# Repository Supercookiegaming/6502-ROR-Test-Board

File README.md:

# 6502-ROR-Test-Board

The 6502 ROR Test Board is a simple computer that tests if the ROR insruction is present on the 6502. I/O space is from 0x0000 to 0x7FFF. Rom space starts at 0x8000 and ends at 0xFFFF. The LED is tied to bit 7 and is set when the CPU R/W is low (writing). The data is then latched into the D-Latch and will be held until updated. The Yes ROR LED is turned on when the cpu writes to any memeory in the I/O space and bit 7 is high, all other bits do nothing. The No ROR LED is turned on whent he cpu writes to any memeory in the I/O space and bit 7 is low.
![ ][logo]

[logo]: https://github.com/Supercookiegaming/6502-ROR-Test-Board/blob/350ec1a620519f19180ad02e0bde4138ba3418b3/Renders/3D/KiCad%209%203D%206502%20ROR%20Test%20Board%20Render%20V2.0T.png
I used https://www.masswerk.at/6502/assembler.html to assemble the rom code and create a BIN file. When using https://www.masswerk.at/6502/# to emulate the board, use the code marked as "Emulator". When the ROR bug is enabled 0x0010 will be 00 and when it is disabled 0x0010 will be 80.

When Building your own board its best to use sockets.

V2.0S uses mostly SMD parts (mostly 0603). V2.0T only has through hole components. 

EasyEDA and KiCad 9 files are now available for both boards. 

The design is free for personally use only.

V2.0S and V2.0T both now support zif sockets for the 6502 and AT28C256, the imporved reset circuit design, ground M3 mounting points, and better silkscreen instructions and pinouts.

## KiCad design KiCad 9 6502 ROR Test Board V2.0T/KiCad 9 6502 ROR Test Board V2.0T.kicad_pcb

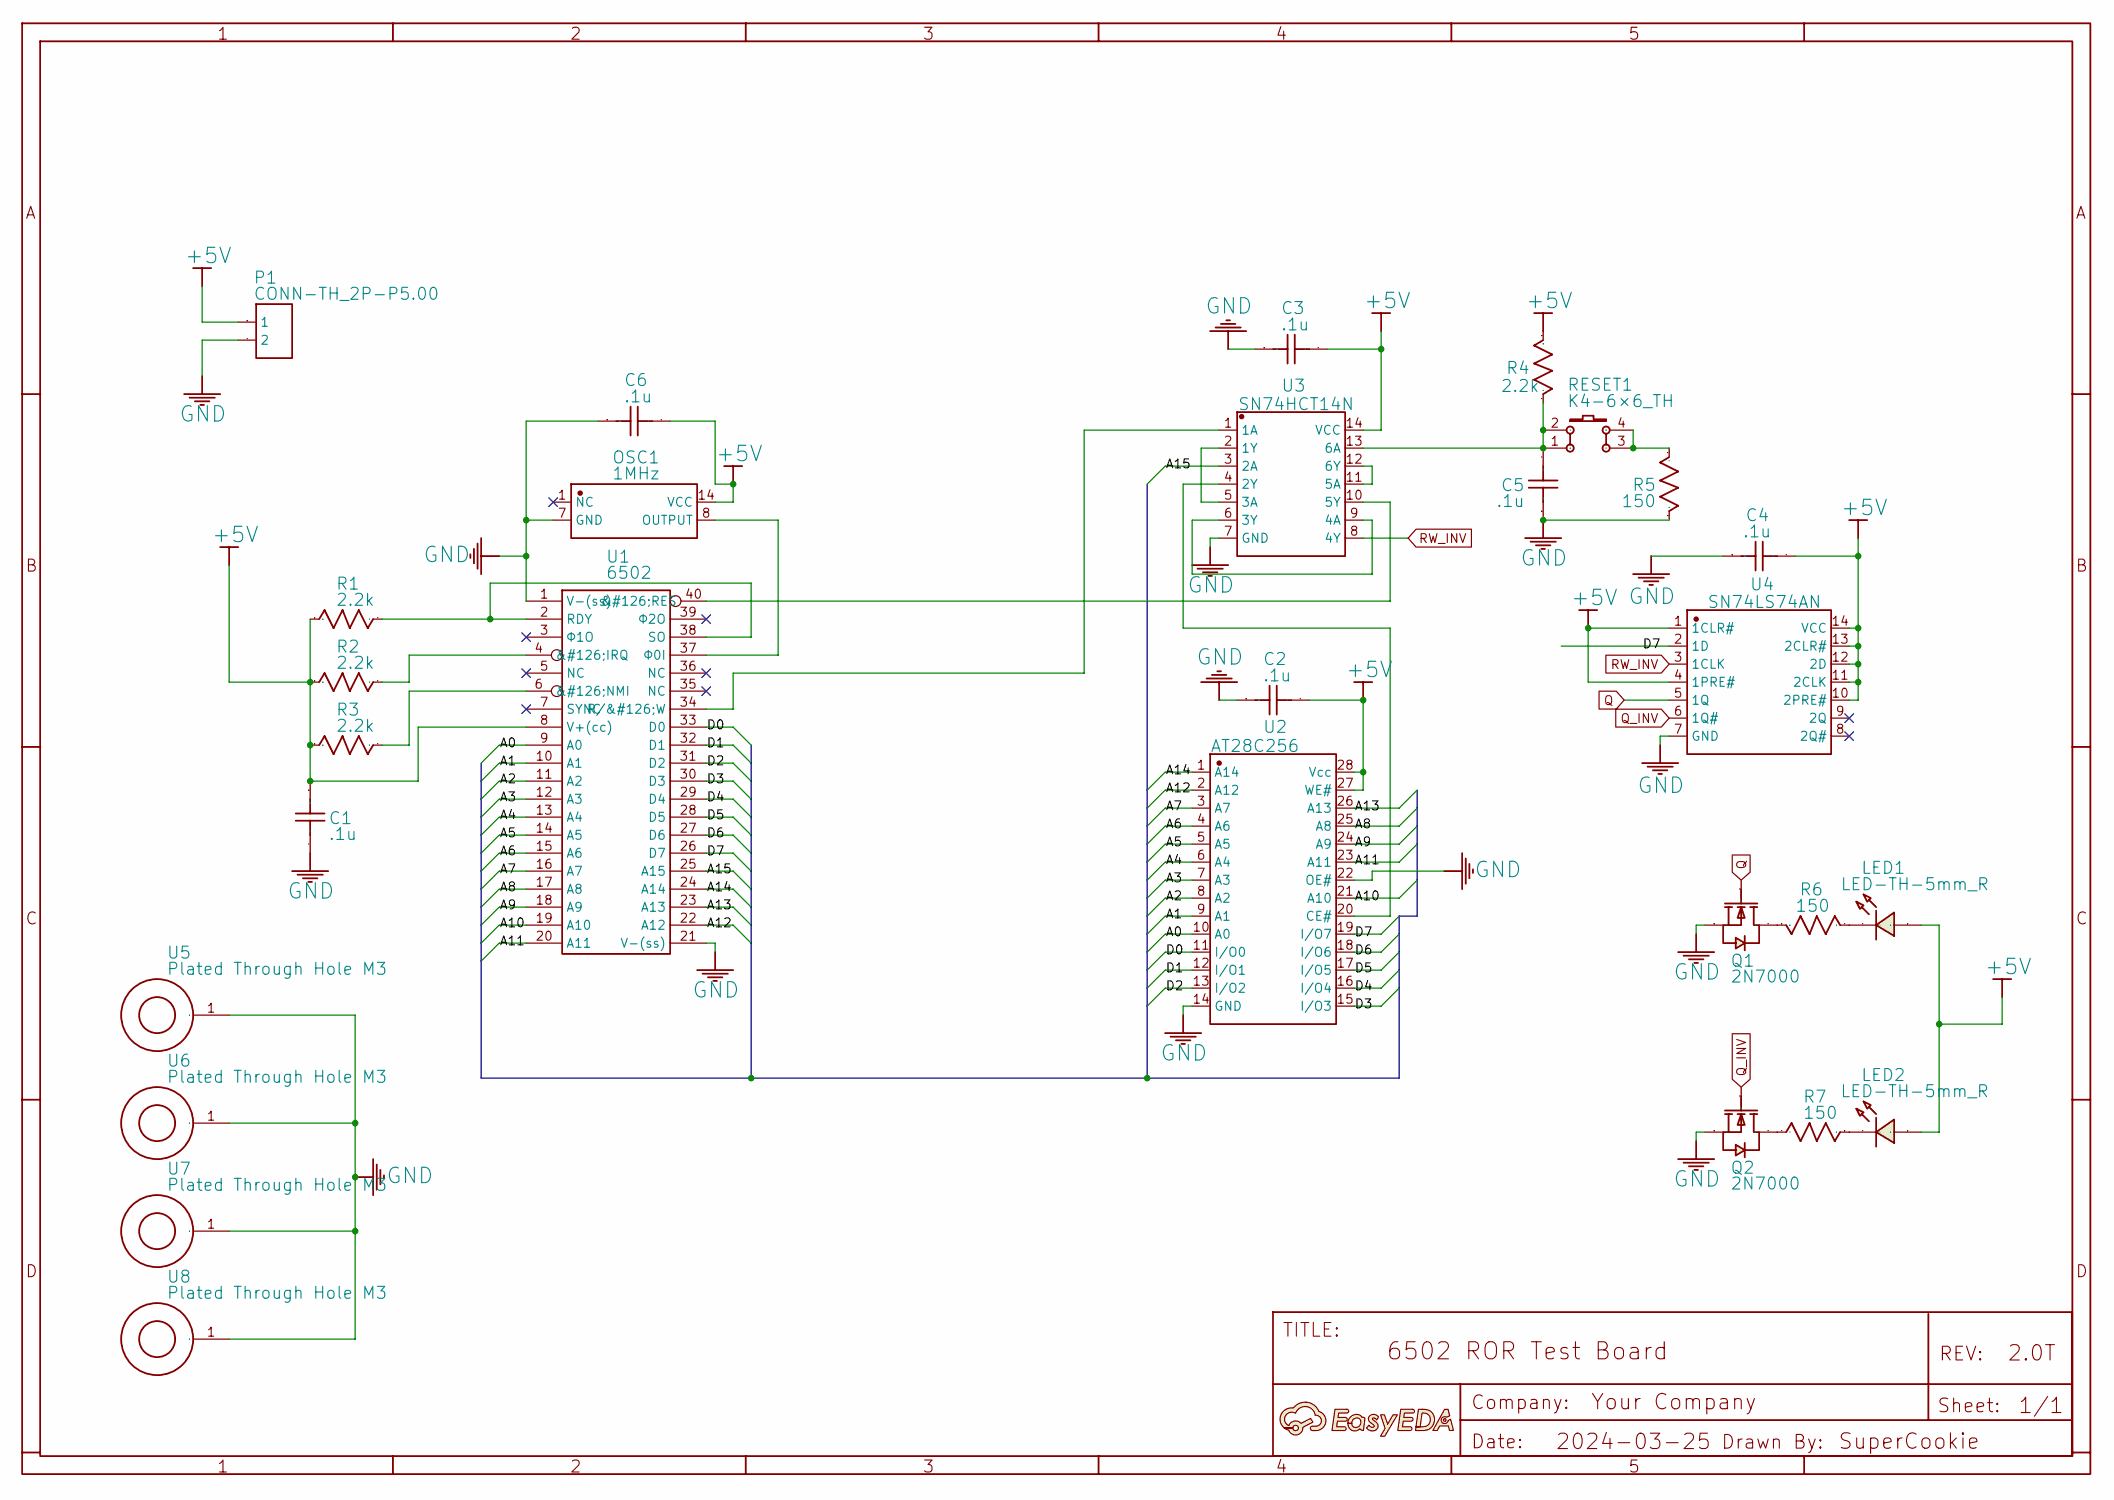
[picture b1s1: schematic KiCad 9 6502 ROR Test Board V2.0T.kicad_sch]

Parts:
A1: A; Manufacturer Part ?
C1, C2, C3, C4, C5, C6: .1u
LED1, LED2: LED-TH-5mm_R; Manufacturer Part 333-2SURD/S530-A3
OSC1: 1MHz; Manufacturer Part MXO45-3C-1M0000
P1: CONN-TH_2P-P5.00
Q1, Q2: 2N7000; Manufacturer Part 2N7002,215
R1, R2, R3, R4: 2.2k
R5, R6, R7: 150
RESET1: K4-6×6_TH; Manufacturer Part K2-1102DP-E4SW-04
U1: 6502
U2: AT28C256; Manufacturer Part AT28C256-15PU
U3: SN74HCT14N; Manufacturer Part SN74HCT14N
U4: SN74LS74AN; Manufacturer Part SN74LS74AN
U5, U6, U7, U8: Plated Through Hole M3

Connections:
+5V: C1.1, C2.2, C3.2, C4.2, C6.2, LED1.1, LED2.1, OSC1.14 (VCC), P1.1, R1.1, R2.1, R3.1, R4.1, U1.8 (V+(cc)), U2.27 (WE#), U2.28 (Vcc), U3.14 (VCC), U4.1 (1CLR#), U4.4 (1PRE#), U4.10 (2PRE#), U4.11 (2CLK), U4.12 (2D), U4.13 (2CLR#), U4.14 (VCC)
/A0: U1.9 (A0), U2.10 (A0)
/A1: U1.10 (A1), U2.9 (A1)
/A2: U1.11 (A2), U2.8 (A2)
/A3: U1.12 (A3), U2.7 (A3)
/A4: U1.13 (A4), U2.6 (A4)
/A5: U1.14 (A5), U2.5 (A5)
/A6: U1.15 (A6), U2.4 (A6)
/A7: U1.16 (A7), U2.3 (A7)
/A8: U1.17 (A8), U2.25 (A8)
/A9: U1.18 (A9), U2.24 (A9)
/A10: U1.19 (A10), U2.21 (A10)
/A11: U1.20 (A11), U2.23 (A11)
/A12: U1.22 (A12), U2.2 (A12)
/A13: U1.23 (A13), U2.26 (A13)
/A14: U1.24 (A14), U2.1 (A14)
/A15: U1.25 (A15), U3.3 (2A)
/D0: U1.33 (D0), U2.11 (I/O0)
/D1: U1.32 (D1), U2.12 (I/O1)
/D2: U1.31 (D2), U2.13 (I/O2)
/D3: U1.30 (D3), U2.15 (I/O3)
/D4: U1.29 (D4), U2.16 (I/O4)
/D5: U1.28 (D5), U2.17 (I/O5)
/D6: U1.27 (D6), U2.18 (I/O6)
/D7: U1.26 (D7), U2.19 (I/O7), U4.2 (1D)
GND: C1.2, C2.1, C3.1, C4.1, C5.1, C6.1, OSC1.7 (GND), P1.2, Q1.1 (S), Q2.1 (S), R5.1, U1.1 (V-(ss)), U1.21 (V-(ss)), U2.14 (GND), U2.22 (OE#), U3.7 (GND), U4.7 (GND), U5.1, U6.1, U7.1, U8.1
unnamed: LED1.2, R6.2
unnamed: LED2.2, R7.1
unnamed: OSC1.8 (OUTPUT), U1.37 (Φ0I)
unnamed: Q1.3 (D), R6.1
unnamed: Q2.3 (D), R7.2
unnamed: R5.2, RESET1.3, RESET1.4
unnamed: R2.2, U1.4 (&#126;IRQ)
unnamed: R3.2, U1.6 (&#126;NMI)
unnamed: U1.40 (&#126;RES), U3.10 (5Y)
unnamed: R1.2, U1.2 (RDY), U1.38 (SO)
unnamed: U1.34 (R/&#126;W), U3.1 (1A)
unnamed: U2.20 (CE#), U3.4 (2Y)
unnamed: U3.2 (1Y), U3.5 (3A)
unnamed: U3.6 (3Y), U3.9 (4A)
unnamed: U3.11 (5A), U3.12 (6Y)
Q: Q1.2 (G), U4.5 (1Q)
Q_INV: Q2.2 (G), U4.6 (1Q#)
R4_2: C5.2, R4.2, RESET1.1, RESET1.2, U3.13 (6A); also elsewhere on the board
RW_INV: U3.8 (4Y), U4.3 (1CLK)

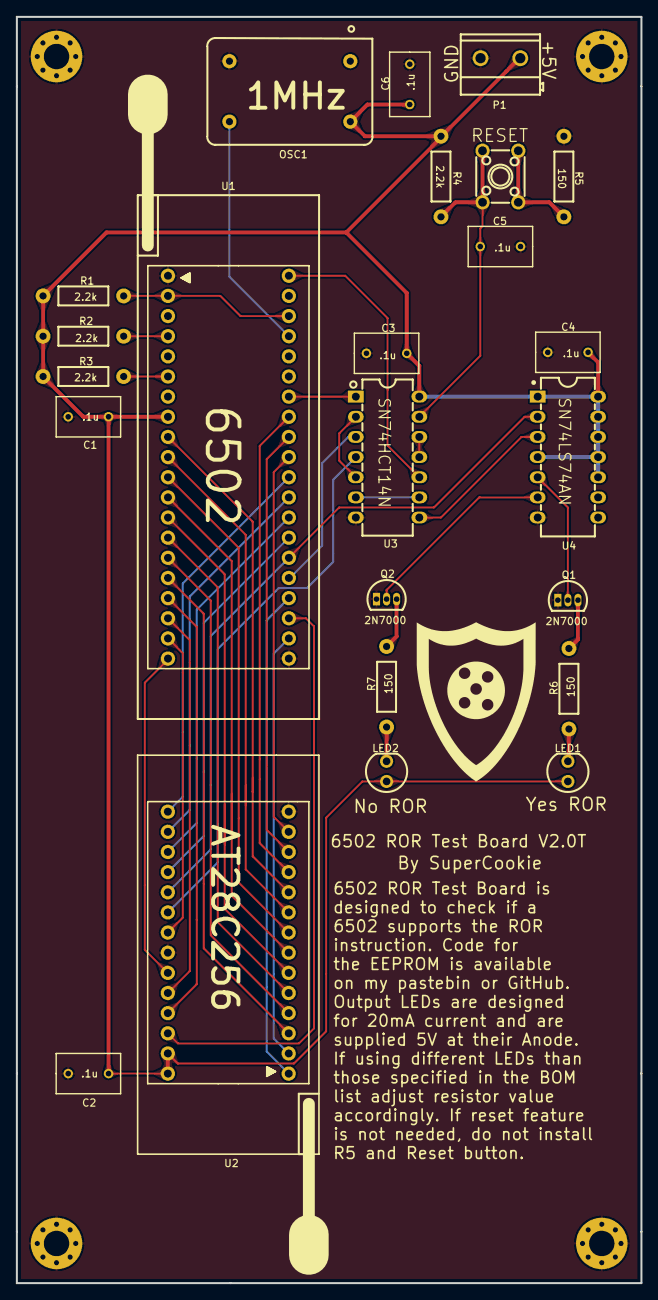
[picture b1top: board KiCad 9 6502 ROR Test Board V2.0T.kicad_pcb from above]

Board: 2 copper layers, 78.7 x 159.6 mm, 28 parts (0 on the bottom side), 45 nets.

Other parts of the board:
RESET: K4-6×6_TH; KEY-TH_4P-L6.0-W6.0-P4.50-LS6.5

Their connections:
R4_2: RESET.1, RESET.2; also elsewhere on the board
R5_2: RESET.3, RESET.4

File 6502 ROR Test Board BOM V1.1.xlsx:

Part | QTY | Link
2.2k Resistor | 4 | https://www.digikey.com/en/products/detail/stackpole-electro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
150 Resistor | 2 | https://www.digikey.com/en/products/detail/stackpole-electro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 |  | * It is strongly recommended to have zif sockets for the 6502 and AT28C256
0.1uF Capacitor | 6 | https://www.mouser.com/ProductDetail/Vishay-BC-Components/K1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
2N7000 | 2 | https://www.digikey.com/en/products/detail/onsemi/2N7000/244278
SN74LS74AN | 1 | https://www.mouser.com/ProductDetail/Texas-Instruments/SN74L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
SN74HCT14N | 1 | https://www.mouser.com/ProductDetail/Texas-Instruments/SN74H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
1Mhz Clock Generator | 1 | https://www.mouser.com/ProductDetail/CTS-Electronic-Componen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
AT28C256 | 1 | https://www.mouser.com/ProductDetail/Microchip-Technology/AT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
6502 | 1
333-2SURD/S530-A3 LED | 2 | https://www.lcsc.com/product-detail/Light-Emitting-Diodes-LE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
2 pin screw terminal | 1 | https://www.mouser.com/ProductDetail/845-30.702
Reset (optional)
6x6mm button | 1 | https://www.digikey.com/en/products/detail/cui-devices/TS02-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
150 Resistor | 1 | https://www.digikey.com/en/products/detail/stackpole-electro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
Normal Dip Sockets (optional*)
40 pin dip socket | 1 | https://www.jameco.com/z/40MTLP-Jameco-ValuePro-40-Pin-Machi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
28 pin dip socket | 1 | https://www.digikey.com/en/products/detail/mill-max-manufact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
14 pin dip socket | 2 | https://www.digikey.com/en/products/detail/on-shore-technolo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
ZIF Sockets (optional*)
40 pin ZIF socket | 1 | https://www.adafruit.com/product/383#description
28 pin ZIF socket | 1 | https://www.ebay.com/itm/264998977768

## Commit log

2023-12-22 Add files via upload
    V1.1 only uses through hole components. replaced the SN74LVC1G373DCKR with a SN74LS00N.
2023-12-22 Add files via upload
    updated source code so processor keeps repeating test instead of just outputting the result of the first test results.
2023-12-22 Rename 6502 ROR Test Board BOM.xlsx to 6502 ROR Test Board BOM V1.0.xlsx
2023-12-22 Rename 6502 ROR Test Board BOM V1.0.xlsx to 6502 ROR Test Board BOM V1.xlsx
2023-12-22 Add files via upload
    changed 2N7002 to correct 2N7000
2023-12-22 Add files via upload
    changed 2N7002 to correct 2N7000. added sockets for 555 and 74LS00
2023-12-23 Add files via upload
    Added EasyEDA files to allow easier modification.
2023-12-24 Updated V1.1 to support optional ZIF sockets
2023-12-24 Cost reduced V1.1
    changed reset circuit to RC type. added push button reset option. reduced cost by remove 555 and changing 74LS00 to a hex shmitt trigger inverter (SN74HCT14N) and a D-Type Latch and Flip-Flop (SN74LS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
2023-12-26 Updated Designes
    Moved V1 to all smd parts (where possible) to reduce size and cost. Updated V1 to have the cheaper/more capable reset circuit of V1.1. Updated silkscreen instructions on both boards. added capacitor 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
2023-12-26 Rename EasyEDA ROR Test Board V1.1.zip to EasyEDA 6502 ROR Test Board V1.1.zip
2023-12-26 added ground m3 mounting holes
2023-12-26 fixed incorrect silkscreen marking
2024-03-26 Updated design
    updated design to add delay to d latch clk input to match requirements of datasheet.
    updated smd design to be easier to solder
    changed naming scheme to so it is easier to differentiate between he SMD and Through hole versions.
    updated BOM to reflect changes
2025-04-16 Added KiCad 9 V2.0S Version
    converted easyeda V2.0S files to KiCad 9 files
2025-04-16 Added KiCad 9 V2.0T Version
    converted easyeda V2.0T files to KiCad 9 files
    renamed renders to EasyEDA Renders
2025-04-16 Added 3D Renders
    Added basic 3D Renders
2025-04-16 Adding 3D models for KiCad V2.0T
2025-04-16 added 3D models to KiCad
    Added 3D Models of components to both KiCad Boards
    Fixed footprint of screw terminal to match with 30.702 on both easyeda and kicad files
    re-rendered 2D view from EasyEDA and added 3D view rendering from KiCad
    Renders in separate folder
    Exported new gerbers from both EasyEDA and KiCad with updated footprint
    Exported 3D model of both boards from KiCad and added to folder.
2025-04-16 KiCad backup update
2025-04-16 Moved Gerbers into New Folder
    moved gerbers into their own folder
2025-04-16 Organized file structure
2025-04-16 Added Code for use in Emulator
2025-05-18 Update README.md
    Fixed image of board in readme
2025-05-18 fixing bin files
2025-06-13 Updated file structure
    -deleted backup files for kicad
    -moved gerber files into gerber subfolder
